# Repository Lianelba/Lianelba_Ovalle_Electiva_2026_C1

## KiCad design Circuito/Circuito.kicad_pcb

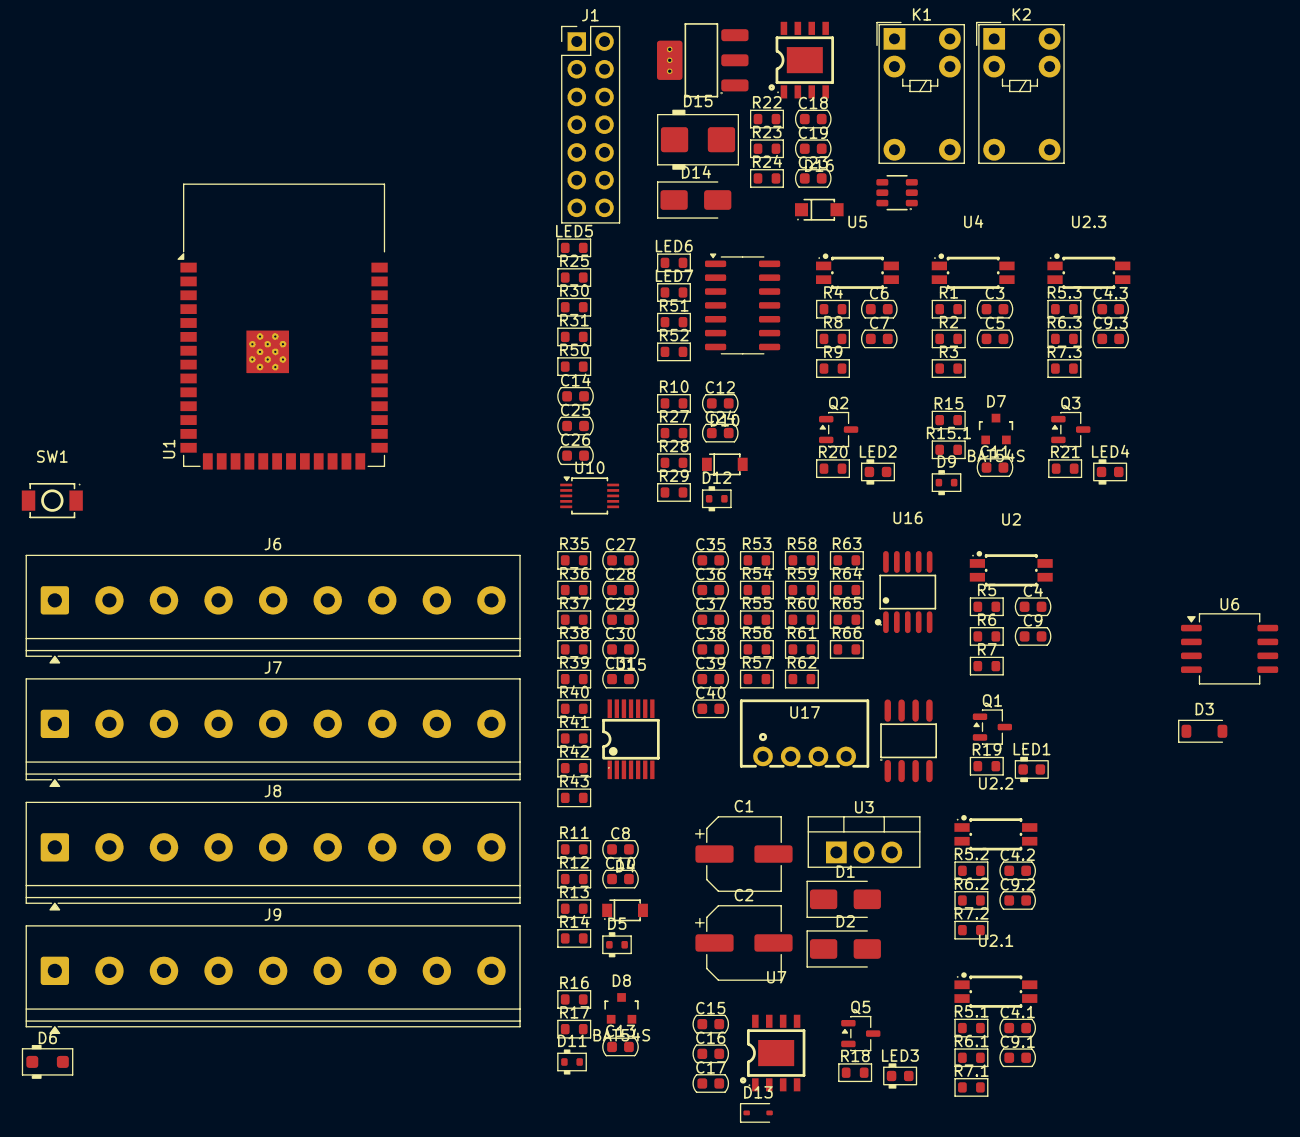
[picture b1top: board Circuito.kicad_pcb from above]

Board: 2 copper layers, 160 parts (0 on the bottom side), 118 nets, no tracks yet.

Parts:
C1, C2: 47UF; CP_Elec_6.3x7.7
C3, C4, C4.1, C4.2, C4.3, C6: 2.2NF; C_0603_1608Metric
C5, C7, C9, C9.1, C9.2, C9.3: 1NF; C_0603_1608Metric
C8, C11, C12, C13, C14, C26, C28, C31, C38, C39, C40: 100NF; C_0603_1608Metric
C10, C24: 47PF; C_0603_1608Metric
C15, C16, C18, C23: C_0603; C_0603_1608Metric
C17: 100nF; C_0603_1608Metric
C19: 1uF; C_0603_1608Metric
C25: 100nf; C_0603_1608Metric
C27, C29, C30: 0.01UF; C_0603_1608Metric
C35, C36: 33NF; C_0603_1608Metric
C37: 68NF; C_0603_1608Metric
D1, D2: SS14; D_SMA
D3: SMF3.3; D_SOD-123
D4, D10: 1N5819HW-7-F; SOD-123_L2.7-W1.6-LS3.7-RD
D5, D9, D11, D12: PESD5Z3.3; D_SOD-523
D6: SMF24CA; D_SOD-123F
D7, D8: BAT54S; SOT23-3_PO132
D13: SD12_SOD323; D_SOD-323
D14: SMAJ12A; D_SMA
D15: SMBJ28A; D_SMB
D16: DSK120_C22466355; SOD-123FL_L2.7-W1.8-LS3.8-RD
J1: Conn_02x07_Odd_Even; PinHeader_2x07_P2.54mm_Vertical
J6, J7, J8, J9: Screw_Terminal_01x09; TerminalBlock_Phoenix_PT-1,5-9-5.0-H_1x09_P5.00mm_Horizontal
K1, K2: G5V-1; Relay_SPDT_Omron_G5V-1
LED1, LED2, LED3, LED4: LED_0603_Red; LED_0603_1608Metric
LED5, LED6, LED7: LED_0603_Red; R_0603_1608Metric
Q1, Q2, Q3, Q5: ZXMS6004FFQTA; SOT-23-3
Q4: NCE60P04R; SOT-223-3_L6.5-W3.4-P2.30-LS7.0-BR
R1, R4, R5, R5.1, R5.2, R5.3: 3.6K; R_0603_1608Metric
R2, R6, R6.1, R6.2, R6.3, R8: 3.3K; R_0603_1608Metric
R3, R7, R7.1, R7.2, R7.3, R9, R25: 22K; R_0603_1608Metric
R10, R12: 120R; R_0603_1608Metric
R11, R27: 49.9R; R_0603_1608Metric
R13, R28: 47K; R_0603_1608Metric
R14, R29: 100K; R_0603_1608Metric
R15, R16, R50: 2.2K; R_0603_1608Metric
R15.1, R17: 1.05K; R_0603_1608Metric
R18, R19, R20, R21, R22, R30, R31, R51, R52: R_0603; R_0603_1608Metric
R23: 470K; R_0603_1608Metric
R24: 15R; R_0603_1608Metric
R35, R36: 0R; R_0603_1608Metric
R37: 20K; R_0603_1608Metric
R38, R39, R40, R41, R42, R43: 150; R_0603_1608Metric
R53, R54: 0.51; R_0603_1608Metric
R55, R56: 1K; R_0603_1608Metric
R57, R59, R60, R61, R62: 390K; R_0603_1608Metric
R58: 510; R_0603_1608Metric
R63, R64, R65, R66: 4.7K; R_0603_1608Metric
SW1: TS-1088-AR02016; SW-SMD_L3.9-W3.0-P4.45
U1: ESP32-S3-WROOM-1
U2, U2.1, U2.2, U2.3, U4, U5: AT3H4B-CUH-S; SSOP-4_L2.7-W4.6-P1.27-LS7.0-TL
U3: PS-TO220; TO-220-3_Vertical
U6: RS485-PROTECT; SOIC-8_5.3x6.2mm_P1.27mm
U7: GP8211S-TC50-EW; ESOP-8_L4.9-W3.9-P1.27-LS6.0-BL-EP
U8: GP8302-TC50-EW; ESOP-8_L4.9-W3.9-P1.27-LS6.0-BL-EP
U9: BTS723GWXUMA1; SOIC-14_L8.7-W3.9-P1.27-LS6.0-BL
U10: ADS1115IDGS; TSSOP-10_3x3mm_P0.5mm
U13: LK1802; SOT-23-6_L2.9-W1.6-P0.95-LS2.8-BR
U15: MAX31856MUD+; TSSOP-14_L5.0-W4.4-P0.65-LS6.4-BL
U16: BL0942; SSOP-10_L4.9-W3.9-P1.00-LS6.0-BL
U17: B0303S-1WR3_C7465185; PWRM-TH_BXXXXS-1WR3
U18: ISO7021DR; SOIC-8_L4.9-W3.9-P1.27-LS6.0-BL

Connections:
+3.3V: C1.1, C2.1, C14.1, C28.1, C31.1, C40.2, D7.2 (cathode), D8.2 (cathode), J1.2, R3.2, R7.2, R7.1.2, R7.2.2, R7.3.2, R9.2, R25.2, R65.2, R66.2, U1.2 (3V3), U3.3 (VO), U6.1 (VCC), U9.11 (SPU), U10.8 (VDD), U15.5 (AVDD), U15.8 (DVDD), U17.2 (+Vin), U18.1 (VCC1)
+5V: D2.2 (A), J1.1
+24V: C4.2, C4.1.2, C4.2.2, C4.3.2, C16.1, C23.1, D1.2 (A), D6.2 (A), D14.1 (A1), J6.1, K1.2, K2.2, R6.1, R6.1.1, R6.2.1, R6.3.1, R18.1, R19.1, R20.1, R21.1, R30.1, U2.2, U2.1.2, U2.2.2, U2.3.2, U7.4 (VCC), U8.4 (VCC), U9.1 (VBB), U9.7 (VBB), U9.8 (VBB), U9.14 (VBB), U13.5 (COM)
/PLC/0-10V_IN1/COM: C13.2, D11.2 (A), R17.2
/PLC/0-10V_IN1/OUT3V: C13.1, D8.3 (AK), D11.1 (K), R16.2, R17.1, U10.7 (AIN3)
/PLC/0-10V_IN/OUT3V: C11.1, D7.3 (AK), D9.1 (K), R15.2, R15.1.1, U10.6 (AIN2)
/PLC/0_10V_1_IN: C11.2, D9.2 (A), J7.2, R15.1, R15.1.2
/PLC/0_10V_2_IN: J7.3, R16.1
/PLC/0_10V_OUT: C17.1, D13.2 (A2), U7.6 (VOUT)
/PLC/4-20mA_1_IN: J7.4, R27.2
/PLC/4-20mA_2_IN: J7.5, R11.2
/PLC/4-20mA_IN1/OUT: C10.1, D5.1 (K), R14.1, U10.5 (AIN1)
/PLC/4-20mA_IN/OUT: C24.1, D12.1 (K), R29.1, U10.4 (AIN0)
/PLC/AC_P: J7.9, R57.1
/PLC/CT_N: J7.6, R54.2, R56.1
/PLC/CT_P: J7.7, R53.1, R55.1
/PLC/EMRX: R66.1, U1.36 (RXD0), U18.2 (OUTA)
/PLC/EM_TX: R65.1, U1.37 (TXD0), U18.3 (INB)
/PLC/EN: C26.2, R25.1, SW1.1, U1.3 (EN)
/PLC/GPIO1: J1.11, U1.8 (IO15)
/PLC/GPIO2: J1.12, U1.9 (IO16)
/PLC/IN_VDC_ADC: C25.1, R30.2, R31.1, U1.6 (IO6)
/PLC/LED_INFO: R50.2, U1.23 (IO21)
/PLC/NPN_1_IN: J6.3, R5.1
/PLC/NPN_1_OUT: J8.6, LED3.1 (K), Q5.3 (D)
/PLC/NPN_1_SIG_IN: U1.27 (IO0), U1.39 (IO1)
/PLC/NPN_1_SIG_OUT: Q5.1 (IN), U1.31 (IO38)
/PLC/NPN_2_IN: J6.4, R5.1.1
/PLC/NPN_2_OUT: J8.7, LED1.1 (K), Q1.3 (D)
/PLC/NPN_2_SIG_OUT: Q1.1 (IN), U1.32 (IO39)
/PLC/NPN_3_IN: J6.5, R5.2.1
/PLC/NPN_3_OUT: J8.8, LED2.1 (K), Q2.3 (D)
/PLC/NPN_3_SIG_OUT: Q2.1 (IN), U1.33 (IO40)
/PLC/NPN_4_IN: J6.6, R5.3.1
/PLC/NPN_4_OUT: J8.9, LED4.1 (K), Q3.3 (D)
/PLC/NPN_4_SIG_OUT: Q3.1 (IN), U1.34 (IO41)
/PLC/NPN_IN1/NPN_1_SIG: C9.1.1, R7.1.1, U2.1.4
/PLC/NPN_IN2/NPN_1_SIG: C9.2.1, R7.2.1, U2.2.4
/PLC/NPN_IN3/NPN_1_SIG: C9.3.1, R7.3.1, U2.3.4
/PLC/NPN_IN/NPN_1_SIG: C9.1, R7.1, U2.4
/PLC/PNP_1_IN: C3.2, J6.7, R2.1, U4.2
/PLC/PNP_1_OUT: J8.4, R51.1, U9.9 (OUT2), U9.10 (OUT2)
/PLC/PNP_1_SIG_IN: C5.1, R3.1, U1.4 (IO4), U4.4
/PLC/PNP_1_SIG_OUT: U1.16 (IO46), U9.2 (IN1)
/PLC/PNP_2_IN: C6.2, J6.8, R8.1, U5.2
/PLC/PNP_2_OUT: J8.5, R52.1, U9.12 (OUT1), U9.13 (OUT1)
/PLC/PNP_2_SIG_IN: C7.1, R9.1, U1.5 (IO5), U5.4
/PLC/PNP_2_SIG_OUT: U1.24 (IO47), U9.6 (IN2)
/PLC/RLY_1_COM: J9.1, K1.5, K1.6
/PLC/RLY_1_NC: J9.3, K1.1
/PLC/RLY_1_NO: J9.2, K1.10
/PLC/RLY_1_OUT: U1.35 (IO42), U13.3 (1B)
/PLC/RLY_2_COM: J9.4, K2.5, K2.6
/PLC/RLY_2_NC: J9.6, K2.1
/PLC/RLY_2_NO: J9.5, K2.10
/PLC/RLY_2_OUT: U1.26 (IO45), U13.4 (2B)
/PLC/RS485-CON: U1.18 (IO10), U6.5 (CON)
/PLC/RS485-RX: U1.12 (IO8), U6.4 (RXD)
/PLC/RS485-TX: U1.17 (IO9), U6.3 (TXD)
/PLC/TEMP_CS: R41.2, U1.25 (IO48)
/PLC/TERMOCUPLA_N: J7.1, R35.1, R37.1
/PLC/TERMOCUPLA_P: J6.9, R36.1
/PLC/clk: J1.9, R40.2, U1.22 (IO14)
/PLC/cs: J1.3, U1.19 (IO11)
/PLC/i2c_scl: J1.10, U1.11 (IO18), U7.1 (SCLK), U8.1 (SLCK), U10.10 (SCL)
/PLC/i2c_sda: J1.8, U1.10 (IO17), U7.2 (SDA), U8.2 (SDA), U10.9 (SDA)
/PLC/miso: J1.7, R39.2, U1.20 (IO12)
/PLC/mosi: J1.5, R38.2, U1.21 (IO13)
/PLC/usb+: J1.4, U1.14 (USB_D+)
/PLC/usb-: J1.6, U1.13 (USB_D-)
Earth: C35.1, C36.2, C37.1, C38.1, C39.1, J7.8, R53.2, R54.1, R58.1, U16.5 (GND), U16.7 (SEL), U17.3 (-Vout), U18.5 (GND2)
GND: C1.2, C2.2, C5.2, C7.2, C8.2, C9.2, C9.1.2, C9.2.2, C9.3.2, C10.2, C12.2, C14.2, C15.2, C16.2, C17.2, C18.2, C19.2, C23.2, C24.2, C25.2, C26.1, C28.2, C29.2, C30.2, C31.2, C40.1, D4.2 (A), D5.2 (A), D6.1 (K), D7.1 (Anode), D8.1 (Anode), D10.2 (A), D12.2 (A), D13.1 (A1), D15.2 (A), J1.13, J1.14, J6.2, J9.9, LED5.1 (K), LED6.1 (K), LED7.1 (K), Q1.2 (OUT), Q2.2 (OUT), Q3.2 (OUT), Q5.2 (OUT), R1.1, R4.1, R10.1, R12.1, R22.2, R23.2, R31.2, SW1.2, U1.1 (GND), U1.40 (GND), U1.41 (GND), U2.3, U2.1.3, U2.2.3, U2.3.3, U3.2 (GND), U4.3, U5.3, U6.2 (GND), U7.5 (GND), U7.9 (EP), U8.5 (GND), U8.9 (EP), U9.4 (GND), U10.1 (ADDR), U10.3 (GND), U13.2 (E), U15.1 (AGND), U15.14 (DGND), U17.1 (-Vin), U18.4 (GND1)
unnamed: C3.1, R1.2, R2.2, U4.1
unnamed: C4.1, R5.2, R6.2, U2.1
unnamed: C4.1.1, R5.1.2, R6.1.2, U2.1.1
unnamed: C4.2.1, R5.2.2, R6.2.2, U2.2.1
unnamed: C4.3.1, R5.3.2, R6.3.2, U2.3.1
unnamed: C6.1, R4.2, R8.2, U5.1
unnamed: C8.1, R13.1, R14.2
unnamed: C12.1, R28.1, R29.2
unnamed: D1.1 (K), D2.1 (K), U3.1 (VI)
unnamed: D4.1 (K), R11.1, R12.2, R13.2
unnamed: D10.1 (K), R10.2, R27.1, R28.2
unnamed: C19.1, D14.2 (A2), Q4.1, R23.1
unnamed: D15.1 (K), Q4.2, Q4.4, R24.1
unnamed: D16.2 (A), R24.2
unnamed: LED1.2 (A), R19.2
unnamed: LED2.2 (A), R20.2
unnamed: LED3.2 (A), R18.2
unnamed: LED4.2 (A), R21.2
unnamed: LED5.2 (A), R50.1
unnamed: LED6.2 (A), R51.2
unnamed: LED7.2 (A), R52.2
unnamed: R57.2, R59.1
unnamed: R59.2, R60.1
unnamed: R60.2, R61.1
unnamed: R61.2, R62.1
unnamed: C15.1, U7.8 (V5V)
unnamed: Q4.3, U8.7 (IOUT)
unnamed: R22.1, U8.6 (SET)
unnamed: C18.1, U8.8 (V5V)
unnamed: K2.9, U13.1 (1C)
unnamed: K1.9, U13.6 (2C)
unnamed: R37.2, U15.2 (BIAS)
unnamed: R40.1, U15.10 (SCK)
unnamed: R38.1, U15.12 (SDI)
unnamed: R39.1, U15.11 (SDO)
unnamed: C27.2, C29.1, R36.2, U15.4 (T+)
unnamed: C27.1, C30.1, R35.2, U15.3 (T-)
unnamed: R41.1, U15.9 (~CS)
unnamed: R43.1, U15.7 (~DRDY)
unnamed: R42.1, U15.13 (~FAULT)
unnamed: C36.1, R56.2, U16.3 (IN)
unnamed: C35.2, R55.2, U16.2 (IP)
unnamed: R63.1, U16.9 (RX/SDI), U18.6 (OUTB)
unnamed: R64.1, U16.10 (TX/SDO), U18.7 (INA)
unnamed: C37.2, R58.2, R62.2, U16.4 (VP)
VCC: C38.2, C39.2, R63.2, R64.2, U16.1 (VDD), U16.8 (SCLK_BPS), U17.4 (+Vout), U18.8 (VCC2)

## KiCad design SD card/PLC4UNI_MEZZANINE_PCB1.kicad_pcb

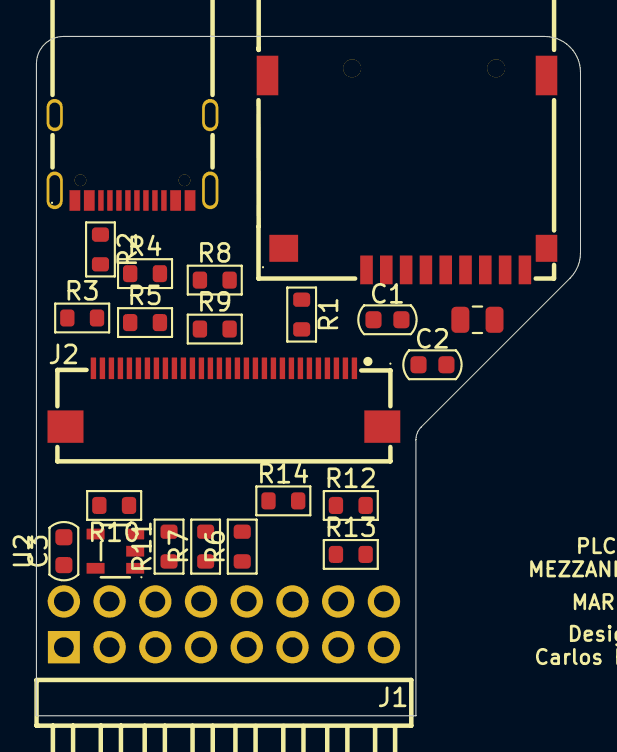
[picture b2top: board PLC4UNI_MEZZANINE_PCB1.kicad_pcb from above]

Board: 2 copper layers, 30.2 x 37.7 mm, 23 parts (0 on the bottom side), 26 nets, no tracks yet.

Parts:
C1: 47uF; C_0603_1608Metric
C2: 100nF; C_0603_1608Metric
C3: 10uF; C_0603_1608Metric
Card1: TF-115; TF-SMD_TF-115
J1: PZ254R-12-16P; HDR-TH_16P-P2.54-H-M-R2-C8-S2.54
J2: FPC-05FB-30PH20; FPC-SMD_30P-P0.50_FPC-05FB-30PH20
L1: 600 Ohm; C_0805_2012Metric
R1, R2: 5.1k; R_0603_1608Metric
R3, R5: 2.2K; R_0603_1608Metric
R4, R8, R9, R12, R13, R14: 10K; R_0603_1608Metric
R6: 10R; R_0603_1608Metric
R7: 220R; R_0603_1608Metric
R10: 6.8K; R_0603_1608Metric
R11: 300; R_0603_1608Metric
U1: MC-121-L119; USB-C-SMD_HANBO_MC-121-L119
U2: MT9700-N; SOT-23-5_L2.9-W1.6-P0.95-LS2.9-BL

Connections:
+3.3V: C3.1, J1.2, L1.2, R3.1, R4.1, R5.1, R8.1, R9.1, R12.1, R13.1, R14.1, U2.5 (VIN)
+5V: J1.1, U1.A4B9 (VBUS), U1.B4A9 (VBUS)
/I2C_SCK: J1.10, J2.26
/I2C_SDA: J1.8, J2.27
/IM2: J2.3, R12.2, R13.2
/LCD_CS: J1.13, J2.6
/LCD_EN: J1.12, U2.4 (EN)
/LED+: J2.20, R11.2
/RESET: J1.11, J2.5, J2.29, R14.2
/SD_CS: Card1.2 (CD/DAT3), J1.3, R9.2
/SPI_CLK: J1.9, J2.7, R6.1
/SPI_MISO: J1.7, J2.19, R5.2, R7.1
/SPI_MOSI: Card1.3 (CMD), J1.5, J2.10, R3.2
/TP_INT: J1.14, J2.28
/USB+: J1.4, U1.A6 (DP1), U1.B6 (DP2)
/USB-: J1.6, U1.A7 (DN1), U1.B7 (DN2)
GND: C1.2, C2.2, C3.2, Card1.6 (VSS), Card1.10 (SHELL), Card1.11 (SHELL), Card1.12 (SHELL), Card1.13 (SHELL), J1.15, J1.16, J2.1, J2.21, J2.22, J2.23, J2.24, J2.30, J2.31, J2.32, R1.2, R2.2, R10.2, U1.13 (EH), U1.A1B12 (GND), U1.B1A12 (GND), U2.2 (GND)
unnamed: Card1.5 (CLK), R6.2
unnamed: Card1.7 (DAT0), R7.2
unnamed: Card1.8 (DAT1), R4.2
unnamed: Card1.1 (DAT2), R8.2
unnamed: C1.1, C2.1, Card1.4 (VDD), L1.1
unnamed: R1.1, U1.A5 (CC1)
unnamed: R2.1, U1.B5 (CC2)
unnamed: R10.1, U2.3 (SET)
VDD: J2.2, J2.25, R11.1, U2.1 (VOUT)

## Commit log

2026-02-04 Primer commit
2026-03-19 commit para yadiel
2026-04-23 Last commit
